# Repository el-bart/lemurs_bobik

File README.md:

# Lemur's Bobik

project of a toy for a 3-5 year child, that is aimed at learning basic programming skills.
robot has 4 buttons for programming directions and one button to start it.

program is generated by a sequence of buttons pressed (eg. forward, forward, left).
after pressing "start" button, robot begins execution of a given sequence.
its programming is thus similar to Logo programming language, but does not require one to be able to read/write, or spending time in front of the screen.

robot's body is designed to mimic a bit autonomous vacuum cleaner robots, that children know and love. :)

## HW parts

* 2x unipolar stepper motors (M42SP-5M - from old desktop printer)
* 12x M3x10 screws
* 12x M3 threaded inserts
* velcro for holding LiPo pack in place (length according to your LiPo size)

## 3D printed parts

`seal` is supposed to be printed in TPU.
after printing, it shall be glued to a `bottom` part with CA glue.
without gluing it will be very hard to put things in place.

all the other elements can be printed in pretty much anything.
my build was just in regular, white PLA.

it's recommend to put some felt under from and rear edges of the bottom part.
it's also worth gluing a thin strip of felt around wheels' external circumference.
this will protect floors from sharp edges and decrease the amount of noise, on flat floors.

while the `seal` is optional, it's highly recommended to silence vibrations.

## electronics

for electronic components checkout BOM, generated by builds, namely:
```
board/hw/control/build/bom.csv
board/hw/buttons/build/bom.csv
```

## known issues

### engines are hard to mount

screws (especially bottom one) are hard to reach.
in a hindsight whole engine-wheel module should have been reworked.
engines could drive wheels directly, and me mounted with threaded inserts.
this would simplify things a lot, and removed noisy gears altogether.

### missing visual feedback

on top panel there should be more LEDs.
these shall indicate:
* button press recorded (possible with dir)
* powered-on state
* low battery state

### batter status

it should be possible to check batter status w/o opening enclosure and disconnecting it.
currently it's very absorbing and inconvenient.

### OTA

programming via AVR's ISP is annoying and requires disassembly.
as of writing these words (HW v2.1) it also requires unplugging main battery (to be fixed in next HW release).
OTA re-flashing would be an improvement.

### debugability

ATtinty2313 in current setting does not have enough pins to provide any feedback (even LED blinking).
more powerful µC should be used instead, that'd allow for serial (or BTLE) port debugging, to monitor state.
on top of that in-system `gdb` would save time for finding stupid mistakes.
this would greatly simplify finding issues and diagnosing inconveniences, that currently require a lot of fuss and re-flashing.

### need better engines

desktop printer engines used require unusual voltage (here: 24V, 0.35A).
they are also quite weak (here: can easily be stopped with 2 fingers).
more powerful NEMA 17 engines would be far superior choice.
using bipolar steppers would also allow to use off the shelve stepper drivers and provide more torque.

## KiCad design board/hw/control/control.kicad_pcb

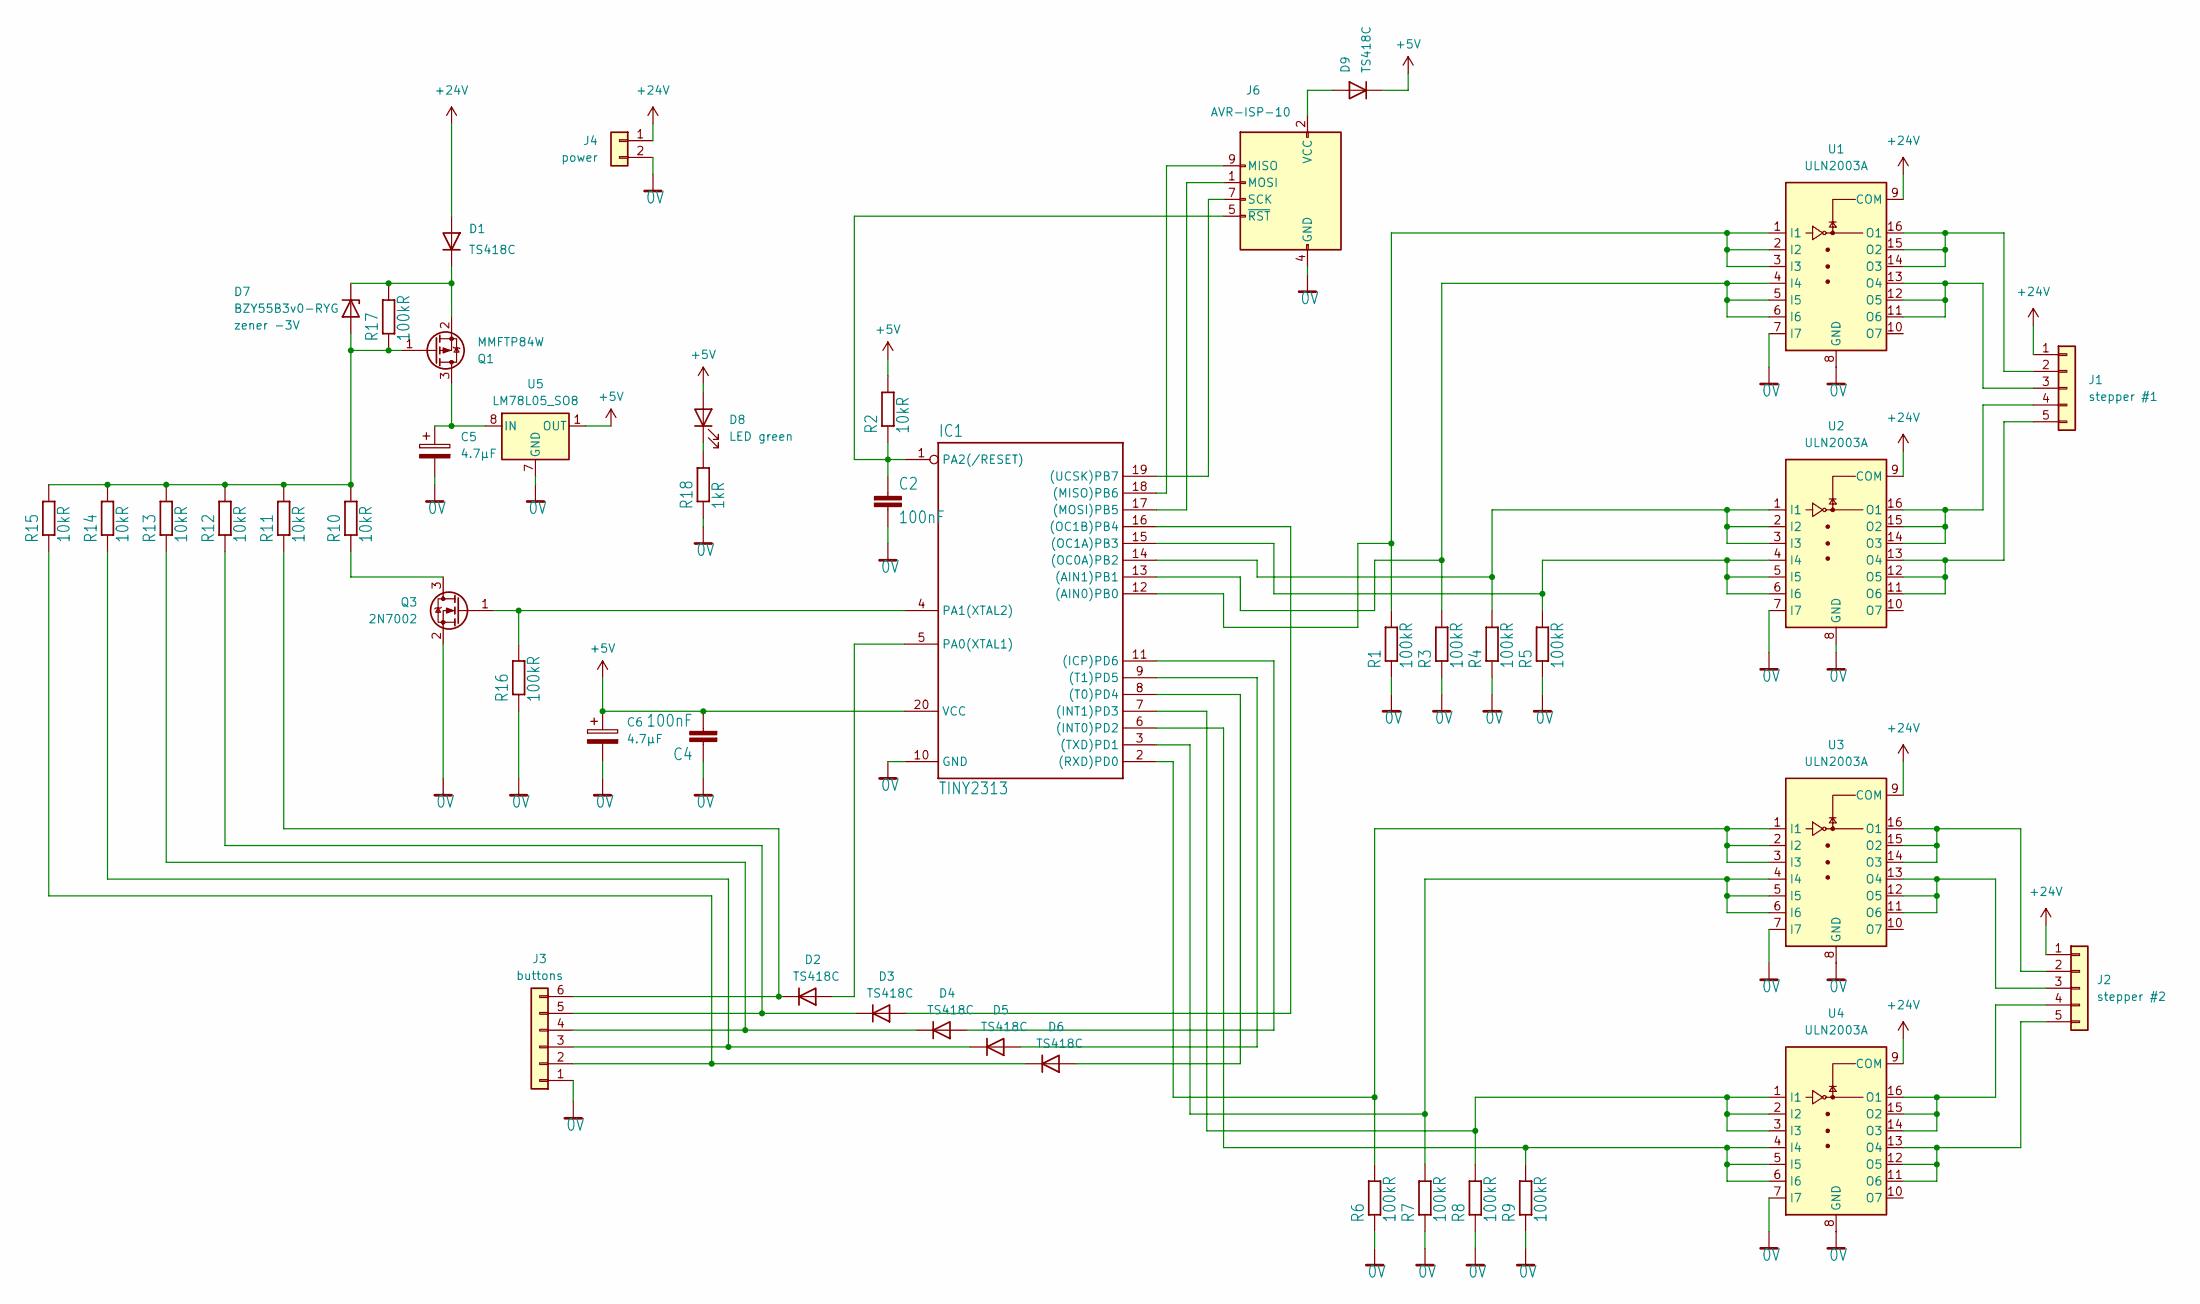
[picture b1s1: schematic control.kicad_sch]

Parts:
C2, C4: 100nF; C_1206_3216Metric_Pad1.33x1.80mm_HandSolder
C5, C6: 4.7µF; CP_Elec_4x5.8
D1, D2, D3, D4, D5, D6, D9: TS418C; D_0805_2012Metric
D7: BZY55B3v0-RYG; D_0805_2012Metric_Pad1.15x1.40mm_HandSolder
D8: LED green; LED_0805_2012Metric_Pad1.15x1.40mm_HandSolder
IC1: TINY2313; SOIC-20W_7.5x12.8mm_P1.27mm
J1: stepper #1; PinHeader_1x05_P2.54mm_Vertical
J2: stepper #2; PinHeader_1x05_P2.54mm_Vertical
J3: buttons; PinSocket_1x06_P2.54mm_Vertical
J4: power; PinHeader_1x02_P2.54mm_Vertical
J6: AVR-ISP-10; IDC-Header_2x05_P2.54mm_Vertical
Q1: MMFTP84W; SOT-323_SC-70
Q3: 2N7002; SOT-23
R1, R3, R4, R5, R6, R7, R8, R9, R16, R17: 100kR; R_0805_2012Metric_Pad1.20x1.40mm_HandSolder
R2, R10, R11, R12, R13, R14, R15: 10kR; R_0805_2012Metric_Pad1.20x1.40mm_HandSolder
R18: 1kR; R_0805_2012Metric_Pad1.20x1.40mm_HandSolder
U1, U2, U3, U4: ULN2003A; SOIC-16_3.9x9.9mm_P1.27mm
U5: LM78L05_SO8; SOIC-8_3.9x4.9mm_P1.27mm

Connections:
0V: C2.2, C4.1, C5.2, C6.2, IC1.10 (GND), J3.1, J4.2, J6.4 (GND), J6.6 (GND), J6.8 (GND), J6.10 (GND), Q3.2 (S), R1.1, R3.1, R4.1, R5.1, R6.1, R7.1, R8.1, R9.1, R16.1, R18.1, U1.7 (I7), U1.8 (GND), U2.7 (I7), U2.8 (GND), U3.7 (I7), U3.8 (GND), U4.7 (I7), U4.8 (GND), U5.2 (GND), U5.3 (GND), U5.6 (GND), U5.7 (GND)
+5V: C4.2, C6.1, D8.2 (A), D9.1 (K), IC1.20 (VCC), R2.2, U5.1 (OUT)
+24V: D1.2 (A), J1.1, J2.1, J4.1, U1.9 (COM), U2.9 (COM), U3.9 (COM), U4.9 (COM)
unnamed: D1.1 (K), D7.1 (K), Q1.2 (S), R17.2
unnamed: D2.2 (A), IC1.5 (PA0(XTAL1))
unnamed: D2.1 (K), J3.6, R11.1
unnamed: D3.2 (A), IC1.16 ((OC1B)PB4)
unnamed: D3.1 (K), J3.5, R12.1
unnamed: D4.2 (A), IC1.11 ((ICP)PD6)
unnamed: D4.1 (K), J3.4, R13.1
unnamed: D5.2 (A), IC1.9 ((T1)PD5)
unnamed: D5.1 (K), J3.3, R14.1
unnamed: D6.2 (A), IC1.8 ((T0)PD4)
unnamed: D6.1 (K), J3.2, R15.1
unnamed: D7.2 (A), Q1.1 (G), R10.2, R11.2, R12.2, R13.2, R14.2, R15.2, R17.1
unnamed: D8.1 (K), R18.2
unnamed: D9.2 (A), J6.2 (VCC)
unnamed: IC1.12 ((AIN0)PB0), R1.2, U1.1 (I1), U1.2 (I2), U1.3 (I3)
unnamed: IC1.13 ((AIN1)PB1), R3.2, U1.4 (I4), U1.5 (I5), U1.6 (I6)
unnamed: IC1.6 ((INT0)PD2), R9.2, U4.4 (I4), U4.5 (I5), U4.6 (I6)
unnamed: IC1.7 ((INT1)PD3), R8.2, U4.1 (I1), U4.2 (I2), U4.3 (I3)
unnamed: IC1.18 ((MISO)PB6), J6.9 (MISO)
unnamed: IC1.17 ((MOSI)PB5), J6.1 (MOSI)
unnamed: IC1.14 ((OC0A)PB2), R4.2, U2.1 (I1), U2.2 (I2), U2.3 (I3)
unnamed: IC1.15 ((OC1A)PB3), R5.2, U2.4 (I4), U2.5 (I5), U2.6 (I6)
unnamed: IC1.2 ((RXD)PD0), R6.2, U3.1 (I1), U3.2 (I2), U3.3 (I3)
unnamed: IC1.3 ((TXD)PD1), R7.2, U3.4 (I4), U3.5 (I5), U3.6 (I6)
unnamed: IC1.19 ((UCSK)PB7), J6.7 (SCK)
unnamed: IC1.4 (PA1(XTAL2)), Q3.1 (G), R16.2
unnamed: C2.1, IC1.1 (PA2(/RESET)), J6.5 (~RST), R2.1
unnamed: J1.2, U1.14 (O3), U1.15 (O2), U1.16 (O1)
unnamed: J1.3, U1.11 (O6), U1.12 (O5), U1.13 (O4)
unnamed: J1.4, U2.14 (O3), U2.15 (O2), U2.16 (O1)
unnamed: J1.5, U2.11 (O6), U2.12 (O5), U2.13 (O4)
unnamed: J2.2, U3.14 (O3), U3.15 (O2), U3.16 (O1)
unnamed: J2.3, U3.11 (O6), U3.12 (O5), U3.13 (O4)
unnamed: J2.4, U4.14 (O3), U4.15 (O2), U4.16 (O1)
unnamed: J2.5, U4.11 (O6), U4.12 (O5), U4.13 (O4)
unnamed: C5.1, Q1.3 (D), U5.8 (IN)
unnamed: Q3.3 (D), R10.1

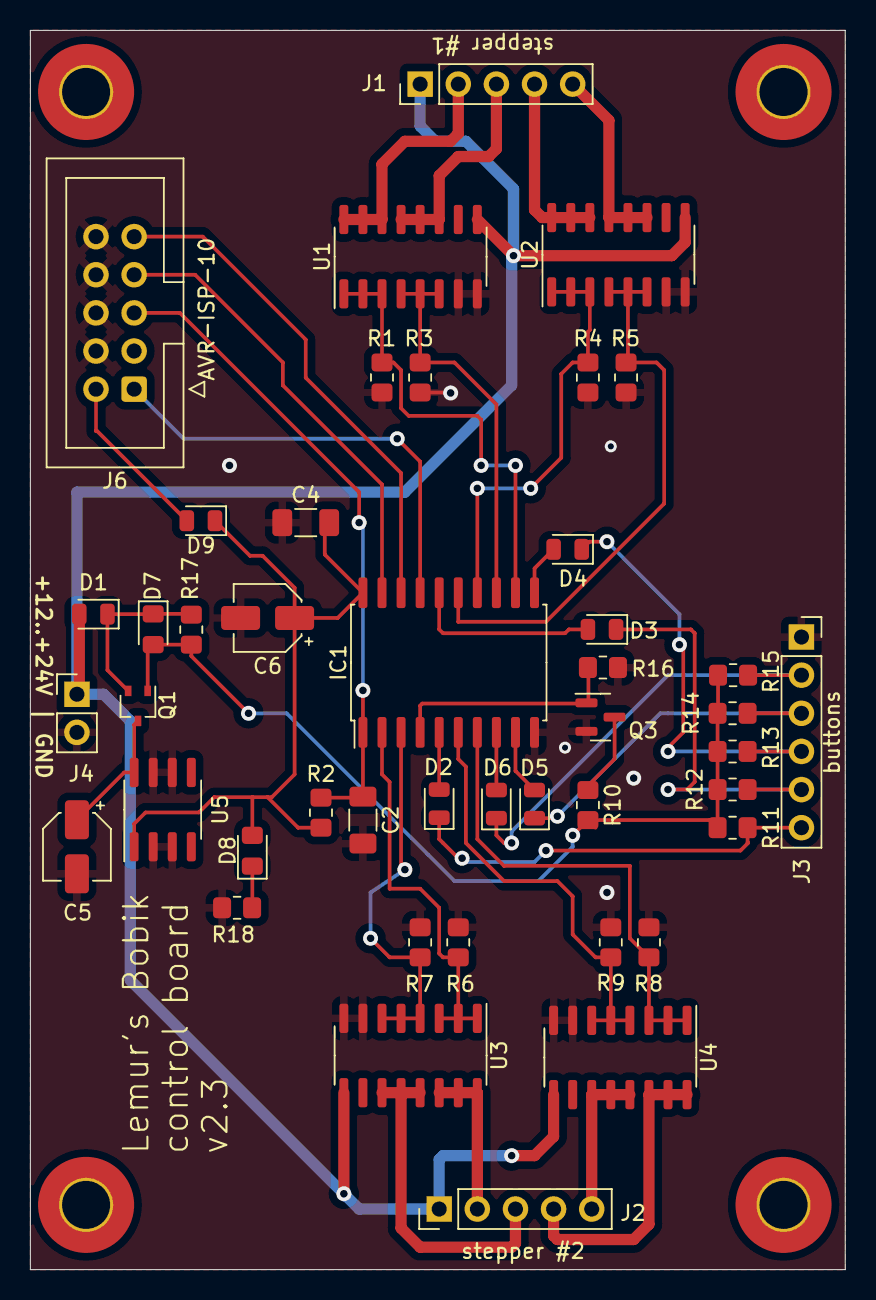
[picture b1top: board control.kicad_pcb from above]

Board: 2 copper layers, 54.3 x 82.5 mm, 48 parts (0 on the bottom side), 40 nets.

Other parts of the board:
1, 2, 3, 4: M3; MountingHole_3.2mm_M3_Pad_TopBottom

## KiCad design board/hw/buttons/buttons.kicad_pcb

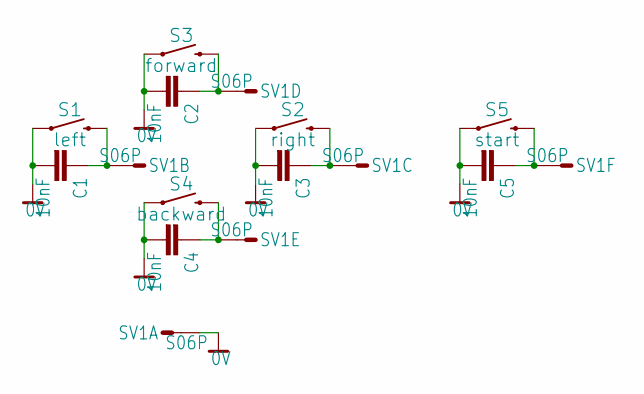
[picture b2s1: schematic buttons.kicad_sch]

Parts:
C1, C2, C3, C4, C5: 10nF; C0805K
S1: left; TACTILE_SWITCH_SMD_12MM
S2: right; TACTILE_SWITCH_SMD_12MM
S3: forward; TACTILE_SWITCH_SMD_12MM
S4: backward; TACTILE_SWITCH_SMD_12MM
S5: start; TACTILE_SWITCH_SMD_12MM
SV1: S06P

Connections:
0V: C1.2, C2.2, C3.2, C4.2, C5.2, S1.1, S2.1, S3.1, S4.1, S5.1, SV1.1
unnamed: C1.1, S1.3 (2), SV1.2
unnamed: C3.1, S2.3 (2), SV1.3
unnamed: C2.1, S3.3 (2), SV1.4
unnamed: C4.1, S4.3 (2), SV1.5
unnamed: C5.1, S5.3 (2), SV1.6

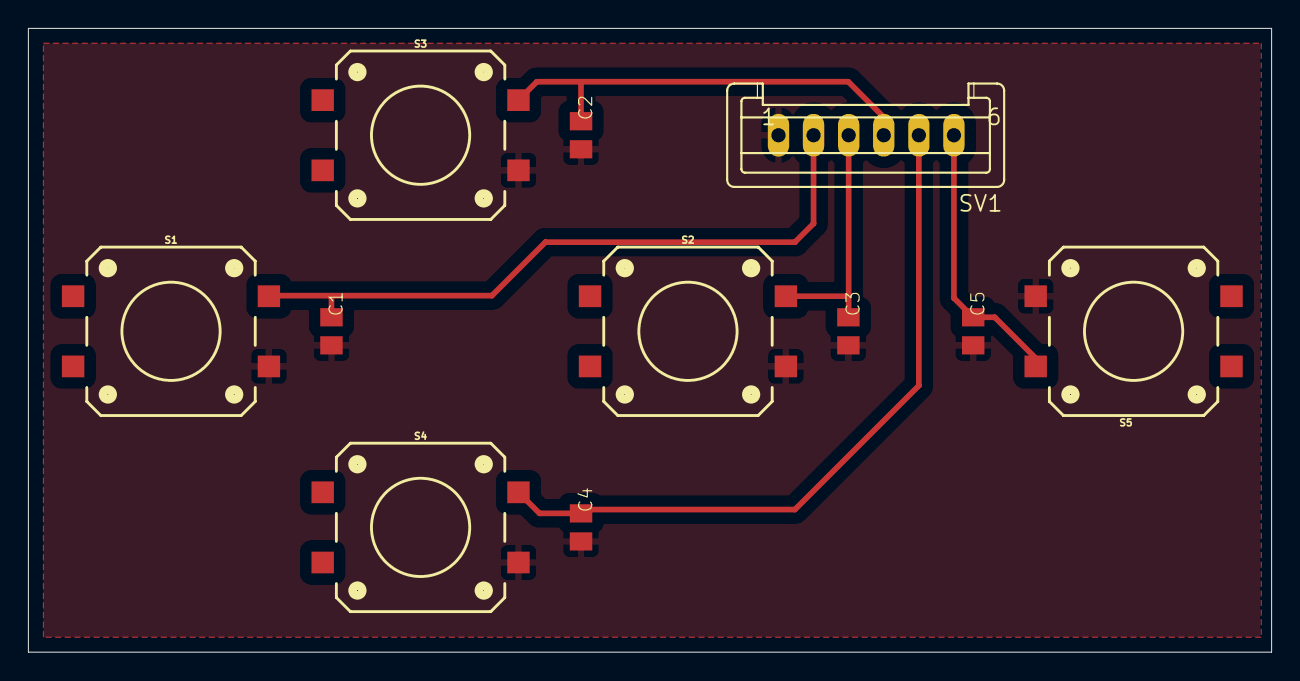
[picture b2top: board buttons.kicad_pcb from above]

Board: 2 copper layers, 88.6 x 44.4 mm, 11 parts (0 on the bottom side), 6 nets.

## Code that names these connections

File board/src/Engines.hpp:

#pragma once
#include "config.hpp"
#include <util/delay.h>

// LEFT  SEQ: PD0 PD2 PD1 PD3
// RIGHT SEQ: PB0 PB2 PB1 PB3
// min  - 15[ms] per step!
// good - 30[ms] per step!

namespace Engines
{

struct PortB
{
  static void init_bits(uint8_t b)   { DDRB |=  b; }
  static void set_bits(uint8_t b)   { PORTB |=  b; }
  static void clear_bits(uint8_t b) { PORTB &= ~b; }
};


struct PortD
{
  static void init_bits(uint8_t b)   { DDRD |=  b; }
  static void set_bits(uint8_t b)   { PORTD |=  b; }
  static void clear_bits(uint8_t b) { PORTD &= ~b; }
};


template<typename Port, uint8_t B0, uint8_t B1, uint8_t B2, uint8_t B3>
struct Generic
{
  Generic() { Port::init_bits( all_bits() ); }
  void off() { Port::clear_bits( all_bits() ); }
  void step_forward() { go_to_pos( next_pos() ); }
  void step_backward() { go_to_pos( prev_pos() ); }

private:
  static auto all_bits() { return B0 | B1 | B2 | B3; }

  void go_to_pos(uint8_t pos)
  {
    off();
    Port::set_bits( pos2bit(pos) );
    pos_ = pos;
  }

  uint8_t pos2bit(uint8_t pos) const
  {
    switch(pos)
    {
      case 0: return B0;
      case 1: return B1;
      case 2: return B2;
      case 3: return B3;
    }
    return 0xFF;    // should never reach here...
  }

  uint8_t next_pos() const
  {
    if(pos_ < 3)
      return pos_ + 1;
    return 0;
  }

  uint8_t prev_pos() const
  {
    if(0 < pos_)
      return pos_ - 1;
    return 3;
  }

  uint8_t pos_{0};
};


using Left  = Generic<PortD, _BV(3), _BV(1), _BV(2), _BV(0)>;
using Right = Generic<PortB, _BV(3), _BV(1), _BV(2), _BV(0)>;

}

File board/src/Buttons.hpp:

#pragma once
#include "config.hpp"

// BUT_UP:    PD6
// BUT_DOWN:  PB4
// BUT_LEFT:  PD4
// BUT_RIGHT: PD5

// BUT_START: PA0


namespace Buttons
{

inline void init()
{
  DDRA  &= ~_BV(0);
  PORTA |=  _BV(0);

  DDRB  &= ~_BV(4);
  PORTB |=  _BV(4);

  DDRD  &= ~( _BV(4) | _BV(5) | _BV(6) );
  PORTD |=    _BV(4) | _BV(5) | _BV(6);
}


inline bool up_pressed()    { return not (PIND & _BV(6)); }
inline bool down_pressed()  { return not (PINB & _BV(4)); }
inline bool left_pressed()  { return not (PIND & _BV(4)); }
inline bool right_pressed() { return not (PIND & _BV(5)); }
inline bool start_pressed() { return not (PINA & _BV(0)); }

inline bool any_pressed()
{
  return up_pressed()    ||
         down_pressed()  ||
         left_pressed()  ||
         right_pressed() ||
         start_pressed();
}

}

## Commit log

2020-04-20 list of ignored elements - basic stuff
2020-04-20 project description
2020-04-20 build for OpenSCAD models
2020-04-20 gear part
2020-04-20 added some basic prints for elements
2020-04-20 ignoring build itme report files
2020-04-20 gear part is a bit more precise with longer teeth + added rod wole in the center
2020-04-20 decreased drive rod hole + added 2 elements on 1 print
2020-04-21 renamed body to enclosure (more accurate)
2020-04-21 build for sw
2020-04-21 simple watchdog wrapper
2020-04-21 application draft
2020-04-21 updated fuse bits to actual project settings
2020-04-21 moved sources next to hardware schematics + added draft of a control board (schematics for now)
2020-04-21 buttons board is ready
2020-04-21 removed capacitors for buttons - these are already covered by the external board
2020-04-21 single-layer routing completed (yay)
2020-04-21 moved KANDA connector in order to simplifiy and reduce board a bit
2020-04-22 decreased board size to cover only copper part
2020-04-23 added 10nF to button boards capacitors
2020-04-23 reorganized labels, so that these fit on the board
2020-04-23 more labels moved not to collide
2020-04-23 moved everything to a bottom layer
2020-04-23 added note on the board, with version
2020-04-23 added board name to a caption
2020-04-24 placeholders for next elements
2020-04-24 main hull + wheel axis mounts
2020-04-24 wheels hole is now bigger and wider
2020-04-24 added engine mounts
2020-04-25 added missing power supply connector
2020-04-28 ignording *.tmp files
2020-04-28 element that can regulat engine mount
2020-04-28 2x engine mount printed at once
2020-04-29 fixed axis diameters/radiuses
2020-04-29 added battery pack mount
2020-04-29 increased height of bobik, so that wheels squeeze in
2020-04-29 added buttons and control board + moved battery pack closer to the center
2020-04-29 electronic mocks added to VCS
2020-04-29 electronics mocks are now printable
2020-04-29 added screw holders for top part + bottom balancing elements
2020-04-29 added reinforcements on the bottom, for better structural rigidity
2020-04-30 bed temperature 60*C -> 50*C as it works far better on large-scale prints
2020-04-30 extrusion width back to 100% decreased 'unstucking' of the PLA on 1st layer
2020-04-30 back to 102% extrusion - it is ok. the unstucking problem was solved with dimafix
2020-05-09 bed tempaerture @ 55*C
2020-07-09 changed ISP programmer type
2020-07-09 moved to internal 128kHz RC oscilator - should be enough i guess
2020-07-09 led blinking equivalnet for start
2020-07-09 Revert "moved to internal 128kHz RC oscilator - should be enough i guess" turned out that 128kHz is TOO SLOW for my progreammer; 1MHz is a must...
    This reverts commit 048d5ced6bc6437dfce4def79e8d7f2b64772a78.
2020-07-09 split target for flashing fuse bits from flashing firmware
2020-07-09 engine spinning test added
2020-07-09 added some test code for buttons - these will need a bit more extra work in HW (pull-ups missing)
2020-07-10 added all the buttons for testing
2020-07-10 added auto-disable all the engines, once the button look is done
2020-07-10 added missing pull-up 100k Rs for all buttons
2020-07-14 added example code that uses all the buttons
2020-07-14 added helper function that tells if any button was pressed
2020-07-14 removed unused header
2020-07-14 engines are now a separate entity
2020-07-14 enabled watchdog
2020-07-14 helper enum with all the directions
2020-07-14 up/down -> fwd/rev
2020-07-14 added algo for reading program from button presses
2020-07-14 main loop consists of simple function calls only, now
2020-07-14 main program execution loop
2020-07-14 removed dead code from main.cpp
2020-07-14 added possiblity to abort program with any button pressed
2020-07-14 watchdog is now namespace not a class + created EnginesControl helper class
2020-07-14 added automatic turning off of all engines when algorithm is stopped (ended or interrupted)
2020-07-14 added a separate function for turning off() engines, as it is used in two places
2020-07-14 extracted steps counts into config.hpp
2020-07-15 correct values for steps per forward/backward and left/right turn
2020-07-15 fixed forward/backward sequences mix
2020-07-16 external gears generation module
2020-07-16 moved to gear ratio 15:20 (i.e. 0.75), for improved speed
2020-07-16 gears.scad is a dependency thus no model is generated for it
2020-07-16 commented out test gear
2020-07-17 build update for OpenSCAD
2020-07-17 removed unused placeholder file
2020-07-17 list of TODOs
2020-07-17 restored original test example parameters
2020-07-17 decreased number of teeth in gears, so that they are smaller and can fit into an existing frame
2020-07-17 scaled the hole so that it fits the actual wheel
2020-07-18 breaking program is now more responsive (1ms instead of 30ms check)
2020-07-18 added wait for all buttons realeased before starting programming + shorter wait for any pressed state
2020-07-18 added extra functionality for waiting for a button press to become a stable one, before declaring it pressed
2020-07-18 decreased ratio to 20:9 (~2.2)
2020-07-18 moving back to original wheel design, just with a ratio around 2.7 instead of 5.4
2020-07-19 moved hole a bit to front, so that smaller gear on the wheel can be compenstated
2020-07-19 new ratio == less steps needed per op
2020-07-20 restored back wheels from before making gear-ratio changes. steppers used are too weak to handle smaller ratios, aspecially on a non-flat surfaces
2020-07-20 removed TODO for decreased gear ratio - did not work out
2020-07-20 Revert "new ratio == less steps needed per op"
    This reverts commit 329b52fe011198930ef57d2dc42e6798ceef3834.
2020-07-26 increased resolution on certain round elements
2020-07-26 TODO for reset button and change of stepper motors
2020-07-26 typos fixes + covid-19 note for parts selsection
2020-07-26 added map cap block, with rounded edges
2020-07-26 added placeholder for cap holes
2020-08-02 top cap model
2020-08-02 MD5 computing support
2020-08-02 ignoring MD5 generated files
2020-08-03 added arrows and start/stop button
2020-08-03 moved capacitor hole closed to the button (where it should be) + fixed main part's resolution
2020-08-03 replaced hardcoded value with a math to get it, so that it is more visible where it comes from
2020-08-03 buttons are now standing out, not being cut-in
2020-08-03 added laser range-finder mock
2022-07-10 fixed typo in TODO.md
2022-07-10 TODO to add some LEDs
2022-07-10 added some photos of the assemly and a final robot, compared to original cleaning robot
2022-07-10 added images to README.md
2023-11-25 updated SDK an set to build in PLA/precise
2023-11-25 moved mocks to detail/
2023-11-25 increased top screw hole diameter, to make a loose fit for M3 bolt
2023-11-25 mock of the stepper motor
2023-11-25 parts list updated (+TODO)
2023-11-25 buttons baord imported into KiCad
2023-11-25 KiCad SDK for buttons
2023-11-25 removed old KiCad project
2023-11-25 control board has been ported to KiCad
2023-11-25 KiCad SDK
2023-11-25 removing old Eagle CAD project of the ctrl board
2023-11-25 holes are no longer highlighted
2023-11-25 moved old stepper motor mock in place of NEMA 17
2023-11-25 removed SDK - it only works for older KiCad
2023-11-25 ground plane is now populated
2023-11-25 added threaded inserts slots for all screws
2023-11-25 TODO: LiPo pack holder
2023-11-25 removed holes for balancing elements - sticking in felt works well enough
2023-11-25 TODO done: threaded inserts are now avaialble
2023-12-02 KiCad automation SDK for both boards
2023-12-02 buttons board converted to newr KiCad
2023-12-02 ctrl board coverted to newer KiCad
2023-12-02 yet one more backup file type...
2023-12-02 moved most elements from Eagle to KiCad libraries
2023-12-02 removed unused elements and added proper AVR-ISP-10 conector
2023-12-02 assigned correct sizes of elements + some draft positioning; still need to add power management cirtcuitry
2023-12-26 added p-mosfet and zerenrs for power ctrl via buttons, too
2023-12-26 PCB routing mostly done - DRC is WIP
2023-12-26 fixed all DRC errors and most warnings
2023-12-26 no more warnings + realigned some silkscreens
2023-12-26 re-enabled all warnings and fixed siklscreen overlapping items
2023-12-26 'stepper #1' silk rotated correctly
2023-12-26 vias for screws moved to MountingHole, so that it's clearly visible in 3D preview
2023-12-26 added control PCB model generated from KiCad
2023-12-26 added mount holes instead of vias + associated mess
2023-12-26 mountholes adjusted to better match existing 3D mount points on the model
2023-12-26 fixed track widths for power lines to steppers
2023-12-26 marked solved TODOs
2023-12-26 added power-on LED to +5V line
2023-12-26 replaced P-MOSFET with N-MOSFET to maintain power-on state
2023-12-26 added PowerCtrl - for now always-on
2023-12-26 implemented auto-power-off when no program is entered withing 2[min]
2023-12-26 no-timeout condition is now a bit more explicit
2023-12-26 update bipolar engine name
2023-12-26 added some more exclusions
2023-12-26 removed TODO, as all's done + updated description to reflect new PCB design
2023-12-26 KiCad SDK updated to latest
2023-12-27 updated KiCad SDK to version exporting drills with gerber, too
2024-01-12 page size adjusted to schematics requirements
2024-01-12 sorking BOM instances
2024-01-13 adjusted programming speed to match µC
2024-01-13 flasing at 1/4 µC's speed, as suggested by datasheet
2024-01-13 fixed bug with not counting timeout properly
2024-01-13 removed dead code
2024-01-13 decreased stepper motors' step delay - with proper power supply we can go much faster
2024-01-14 engines directions are swaped
2024-01-14 increased buttons sensitivity
2024-01-14 fine-tuned moving speed
2024-01-14 TODO to optimize keyboard usage
2024-01-14 C2 and C4 are not 1206 as they should
2024-01-14 re-filled zones
2024-01-14 project updated
2024-01-14 removed old battery pack holder
2024-01-14 batter slot is now for velcro + LiPo pack
2024-01-14 added note on velcro for holding LiPo
2024-01-14 added FAQ section
2024-01-14 updated list of screws and nuts + BOM for electronic components
2024-01-14 updated pictured and removed (now outdated) FAQ
2024-01-14 removed FAQ (this time for real)
2024-01-14 electornics moved to a separate section
2024-01-14 updated PCB version
2024-01-14 improved input buttons filtering, to ensure more responsive (and reliable) input
2024-01-14 fixed the issue where wake-up button press was not added to program sequence
2024-01-14 decreased speed of steppers a bit
2024-01-14 added exact type of steppers
2024-01-14 adjusted travelved dsistance params
2024-01-14 decreased number of directions to 30 (RAM)
2024-01-14 more draconian accurate algo of reading key presses
2024-01-14 lsessions learned / known issues
2024-01-14 adjusted for forward-steps
2024-01-14 yet another buttons tunning
2024-01-14 added diade so that AVR's ISP can optionaly power the board, but board power will not damage the programmer
2024-01-16 perfect 360*deg turn :)
2024-01-23 KiCad SDK v2.2
2024-01-24 moved common numbers into shared code part
2024-01-24 added seal model
2024-01-24 aggresive usage of m3d's fn() for faster previews
2024-01-24 added cylinder_h as a common param, too
2024-01-24 renamed main module to align with file name + removed bottom visuzalitaion
2024-01-24 added visualizatrion of both top() and seal() in preview
2024-01-24 added preview of top and seal by default
2024-01-24 3D SDK upgrade
2024-01-24 pcb_control.stl is now to be copied from the control board's build
2024-01-24 printing seal in TPU, solid but w/o ironing, as it does not need to be waterproof - it's just about shock absorbtion
2024-01-25 some hints on 3D printed elements and felt placement
2024-09-20 fixed a couple typos
2024-09-20 KiCad SDK update for buttons board
2024-09-20 KiCad SDK update for control board
